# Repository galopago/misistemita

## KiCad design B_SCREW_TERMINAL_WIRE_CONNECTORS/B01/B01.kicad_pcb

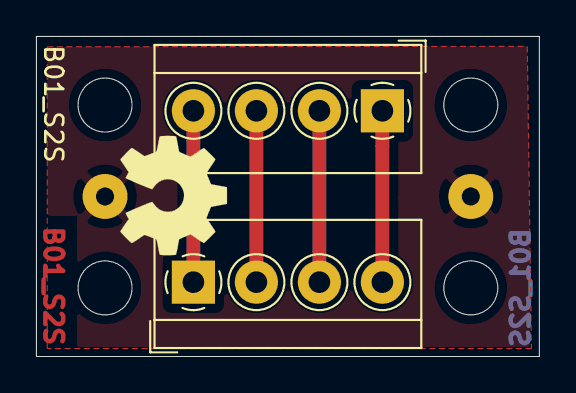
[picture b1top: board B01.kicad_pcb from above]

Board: 2 copper layers, 27.9 x 17.8 mm, 8 parts (0 on the bottom side), 5 nets.

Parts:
HA0, HA2: MountingHole; MountingHole_3mm
HB0, HB2: MountingHole; MountingHole_3mm
J0, J1: Conn_01x01_Male; SolderWirePad_1x01_Drill1mm
J4, J5: Conn_01x04_Female; TerminalBlock_4Ucon_1x04_P3.50mm_Horizontal

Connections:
unnamed: J0.1, J1.1
unnamed: J4.1, J5.4
unnamed: J4.2, J5.3
unnamed: J4.3, J5.2
unnamed: J4.4, J5.1

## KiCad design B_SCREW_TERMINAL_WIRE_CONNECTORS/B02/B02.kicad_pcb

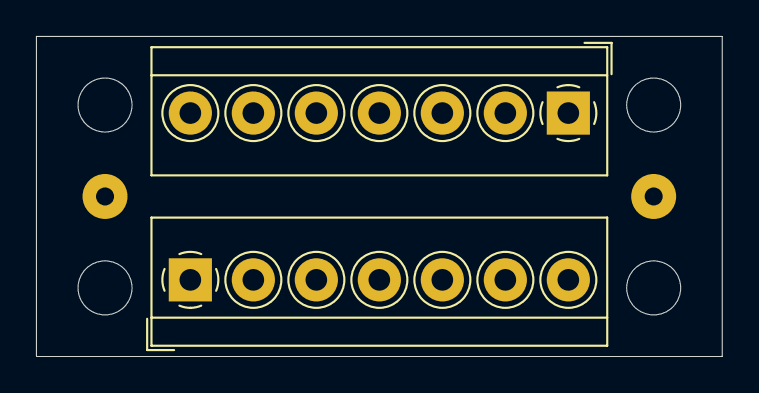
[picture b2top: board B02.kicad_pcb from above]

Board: 2 copper layers, 38.1 x 17.8 mm, 8 parts (0 on the bottom side), 8 nets, no tracks yet.

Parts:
HA0, HA3: MountingHole; MountingHole_3mm
HB0, HB3: MountingHole; MountingHole_3mm
J0, J1: Conn_01x01_Male; SolderWirePad_1x01_Drill1mm
J4, J5: Conn_01x07_Female; TerminalBlock_4Ucon_1x07_P3.50mm_Horizontal

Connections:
unnamed: J0.1, J1.1
unnamed: J4.1, J5.7
unnamed: J4.2, J5.6
unnamed: J4.3, J5.5
unnamed: J4.4, J5.4
unnamed: J4.5, J5.3
unnamed: J4.6, J5.2
unnamed: J4.7, J5.1
